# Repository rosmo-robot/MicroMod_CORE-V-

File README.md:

# MicroMod_CORE-V-
Developing a MicroMod board for the CORE-V 

https://www.openhwgroup.org/core-v-devkits/

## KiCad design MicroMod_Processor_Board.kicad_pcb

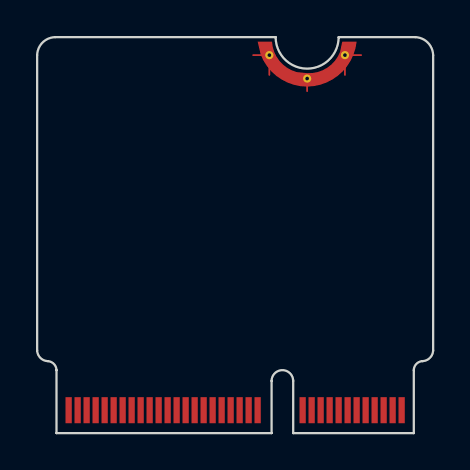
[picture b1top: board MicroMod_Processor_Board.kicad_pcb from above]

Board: 4 copper layers, 22.0 x 22.0 mm, 4 parts (1 on the bottom side), 6 nets, no tracks yet.

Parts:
FRAME1: FRAME-LEDGER; CREATIVE_COMMONS
J1: MICROMOD-2222; M.2-CARD-E-22
LOGO1: SPECIAL_INSTRUCTIONS-ORDERING; ORDERING_INSTRUCTIONS
LOGO3: OSHW-LOGOS; OSHW-LOGO-S

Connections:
3.3V: J1.2, J1.74
/16-G4/RX1/AUD_IN: J1.19, J1.48, J1.54
/17-G3/TX1/AUD_OUT: J1.17, J1.46, J1.56
/25-G1/AUD_LRCLK/SCL1: J1.42, J1.52, J1.53
/26-G2/AUD_BCLK/SDA1: J1.44, J1.50, J1.51
GND: J1.1, J1.7, J1.33, J1.36, J1.39, J1.45, J1.75, J1.GND1, J1.GND2, J1.GND3

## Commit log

2023-02-20 Create LICENSE.txt
    CERN-OHL-P https://ohwr.org/cern_ohl_p_v2.txt

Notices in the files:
parts and their libraries:
Released under the CERN-OHL-P-License
